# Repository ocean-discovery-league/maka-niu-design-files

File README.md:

# maka-niu-design-files
All files needed to build a Maka Niu

Instructions for fabrication and software installation here.

Link to install image here.
 
Please direct all questions concerning fabrication plans or direct purchase of the Delrin housing to Dr. Allan Adams of Oceanic Labs (allan@oceanic-labs.org)

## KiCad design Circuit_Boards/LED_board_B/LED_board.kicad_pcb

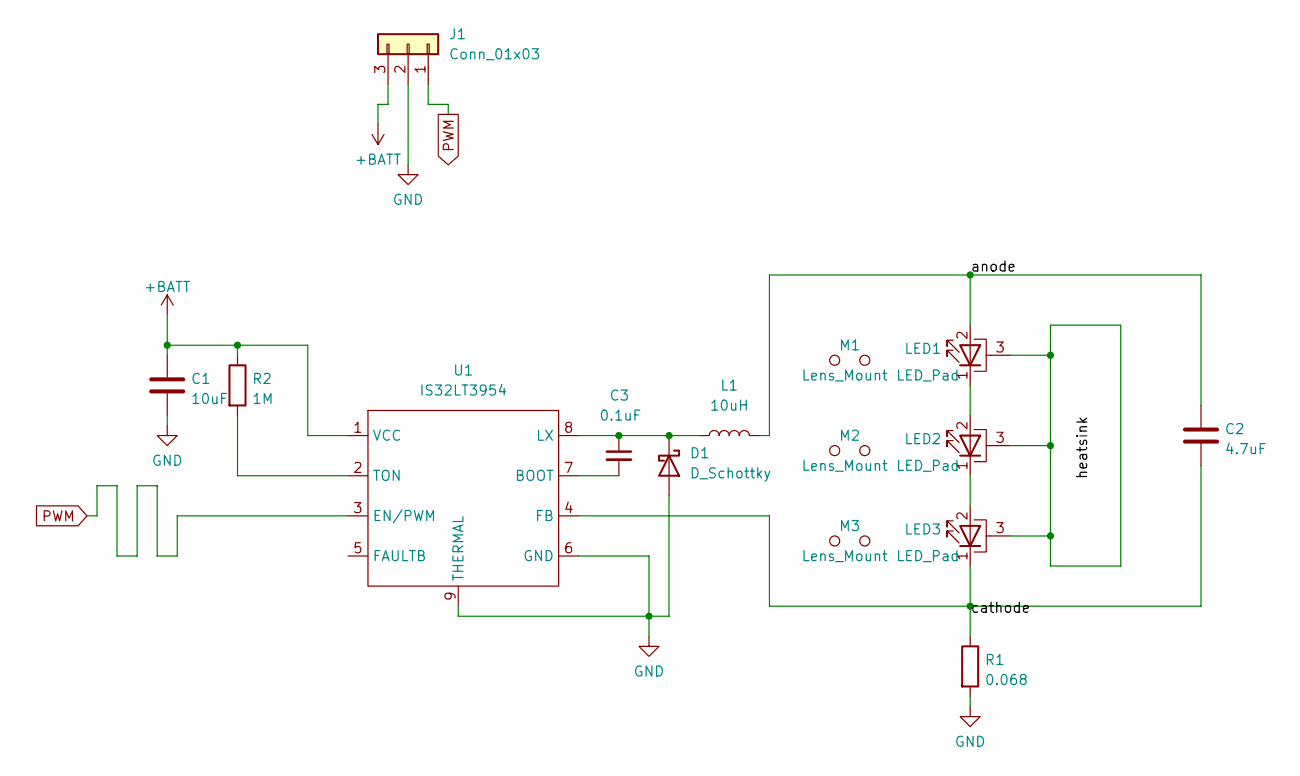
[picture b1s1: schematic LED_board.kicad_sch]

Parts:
C1: 10uF; C_1210_3225Metric; Digikey 13-CC1210KFX7R8BB106CT-ND
C2: 4.7uF; C_1210_3225Metric; Digikey 1276-1292-1-ND
C3: 0.1uF; C_0603_1608Metric; Digikey 1276-1935-1-ND
D1: D_Schottky; D_SMA; Digikey SK54A-LTPMSCT-ND
J1: Conn_01x03; Molex_Micro-Fit_3.0_43650-0324_1x03-1MP_P3.00mm_Vertical; Digikey WM3887CT-ND
L1: 10uH; PA5175_Inductor; Digikey 553-PA5175.103NLTCT-ND
LED1, LED2, LED3: LED_Pad; LED_Cree-XHP50_3V_hand_solder; Digikey XMLBWT-00-0000-0000U2050CT-ND
M1, M2, M3: Lens_Mount; LEDiL_Clip; Digikey 711-FP18200_LISA3-M-CLIP16-ND
R1: 0.068; R_2512_6332Metric; Digikey 311-0.068TCT-ND
R2: 1M; R_0603_1608Metric; Digikey RMCF0603FG1M00CT-ND
U1: IS32LT3954; SOP-8-1EP_4.57x4.57mm_P1.27mm_EP4.57x4.45mm_ThermalVias; Digikey 2521-IS32LT3954-GRLA3-TRCT-ND

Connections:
+BATT: C1.1, J1.3, R2.1, U1.1 (VCC)
/anode: C2.1, L1.2, LED1.2 (A)
/cathode: C2.2, LED3.1 (K), R1.1, U1.4 (FB)
/heatsink: LED1.3 (PAD), LED2.3 (PAD), LED3.3 (PAD)
GND: C1.2, D1.2 (A), J1.2, R1.2, U1.6 (GND), U1.9 (THERMAL)
unnamed: C3.1, D1.1 (K), L1.1, U1.8 (LX)
unnamed: C3.2, U1.7 (BOOT)
unnamed: LED1.1 (K), LED2.2 (A)
unnamed: LED2.1 (K), LED3.2 (A)
unnamed: R2.2, U1.2 (TON)
PWM: J1.1, U1.3 (EN/PWM)

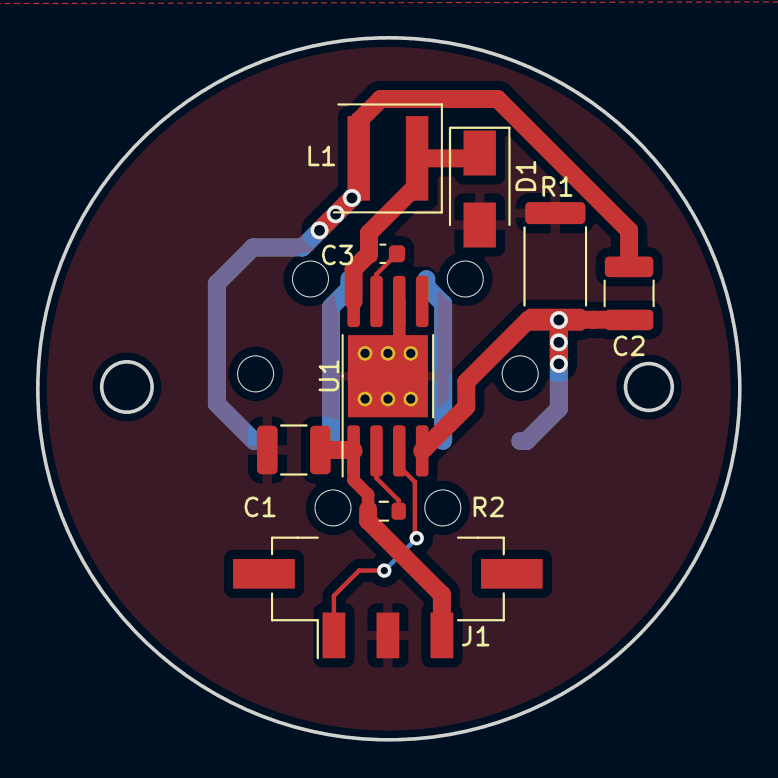
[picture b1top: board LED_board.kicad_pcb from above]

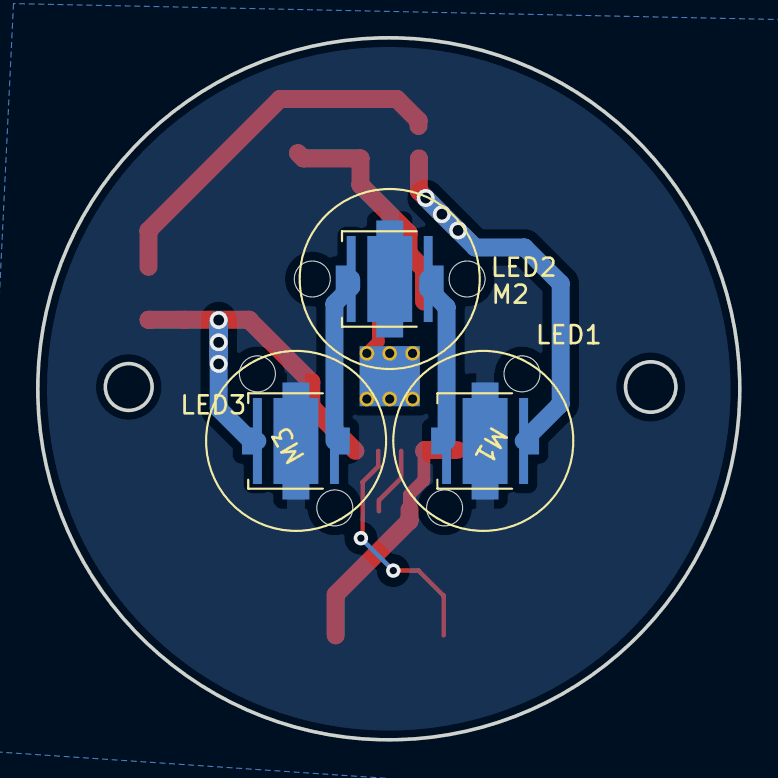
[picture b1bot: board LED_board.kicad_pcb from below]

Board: 2 copper layers, 39.0 x 39.0 mm, 15 parts (6 on the bottom side), 11 nets.

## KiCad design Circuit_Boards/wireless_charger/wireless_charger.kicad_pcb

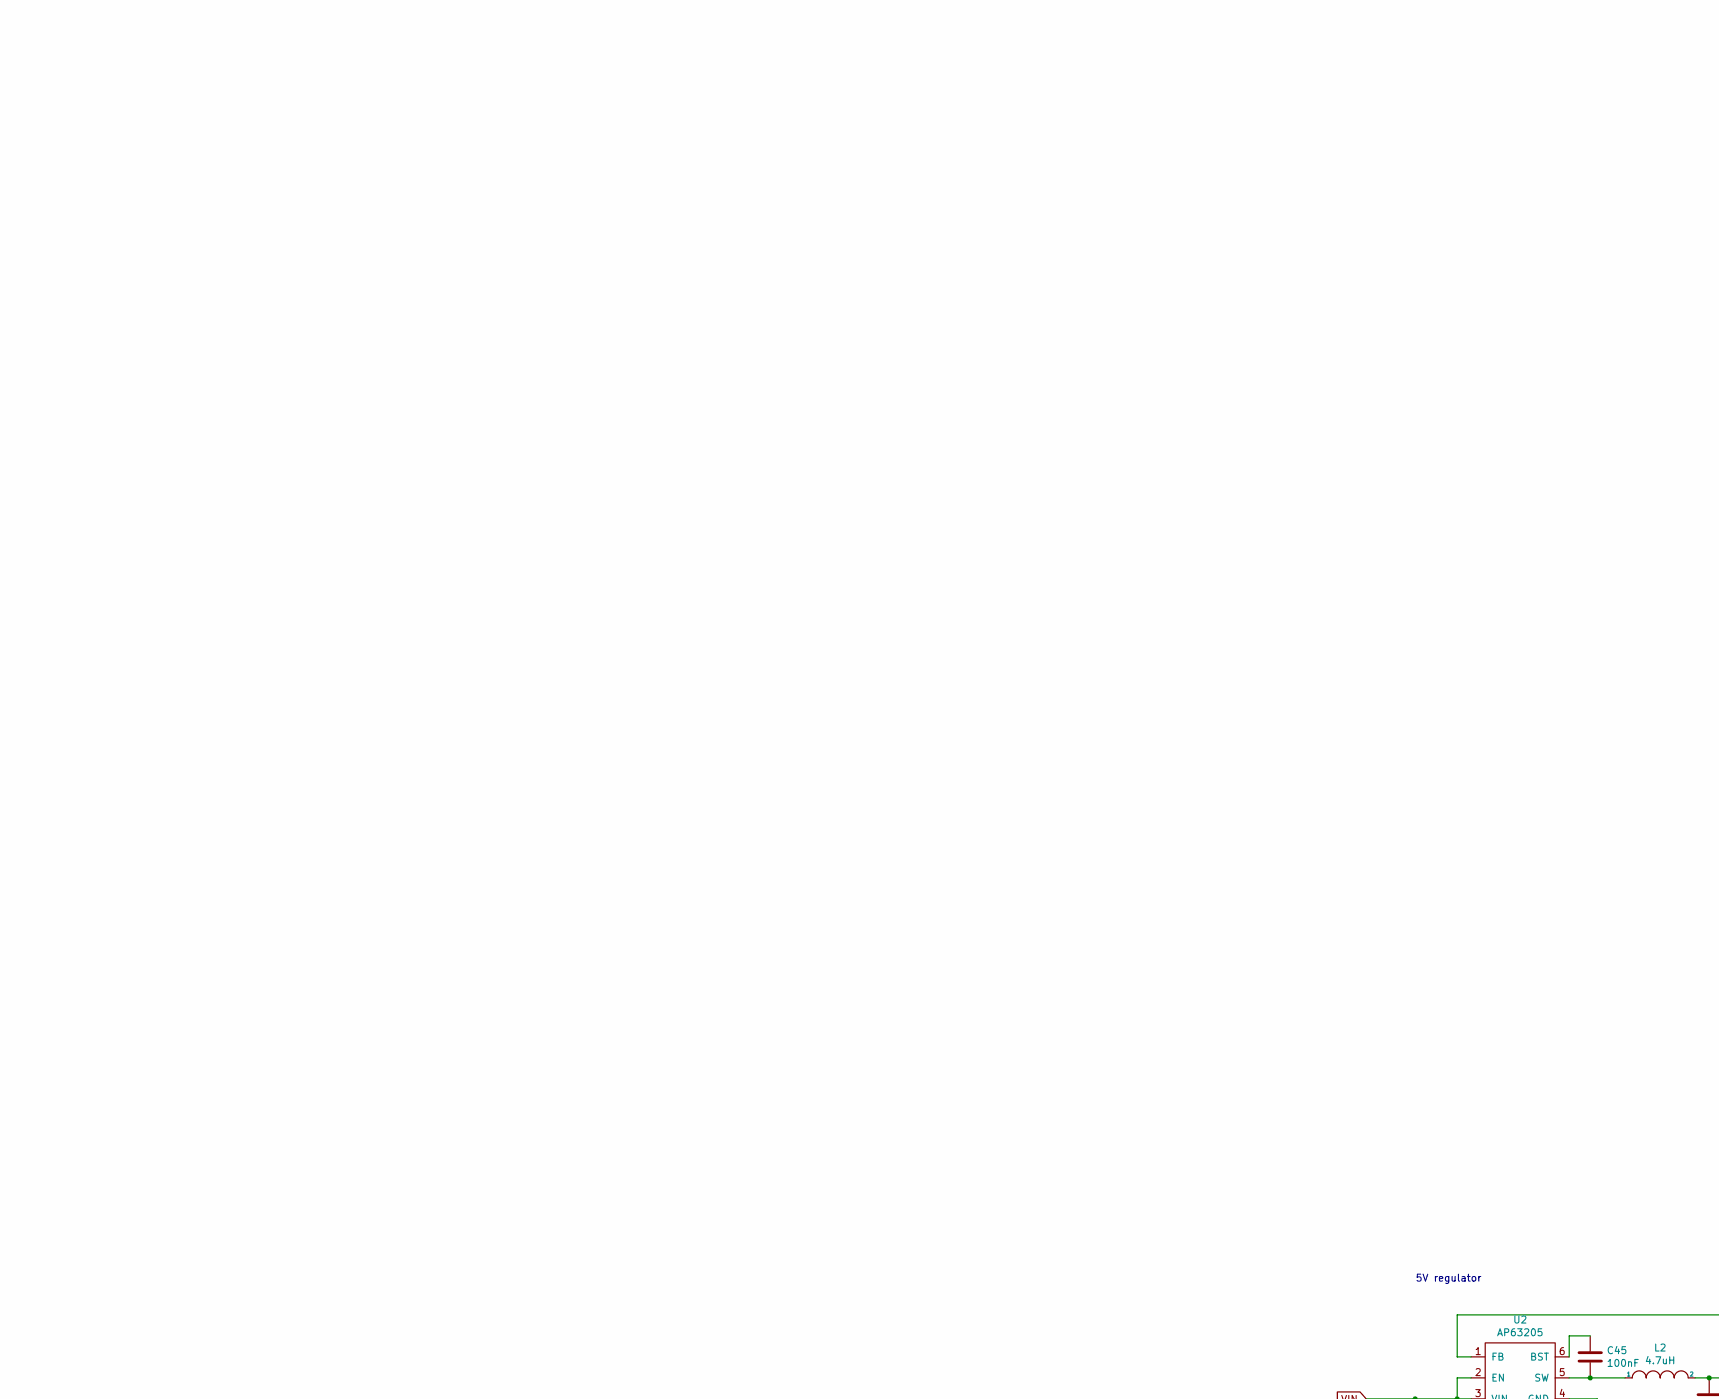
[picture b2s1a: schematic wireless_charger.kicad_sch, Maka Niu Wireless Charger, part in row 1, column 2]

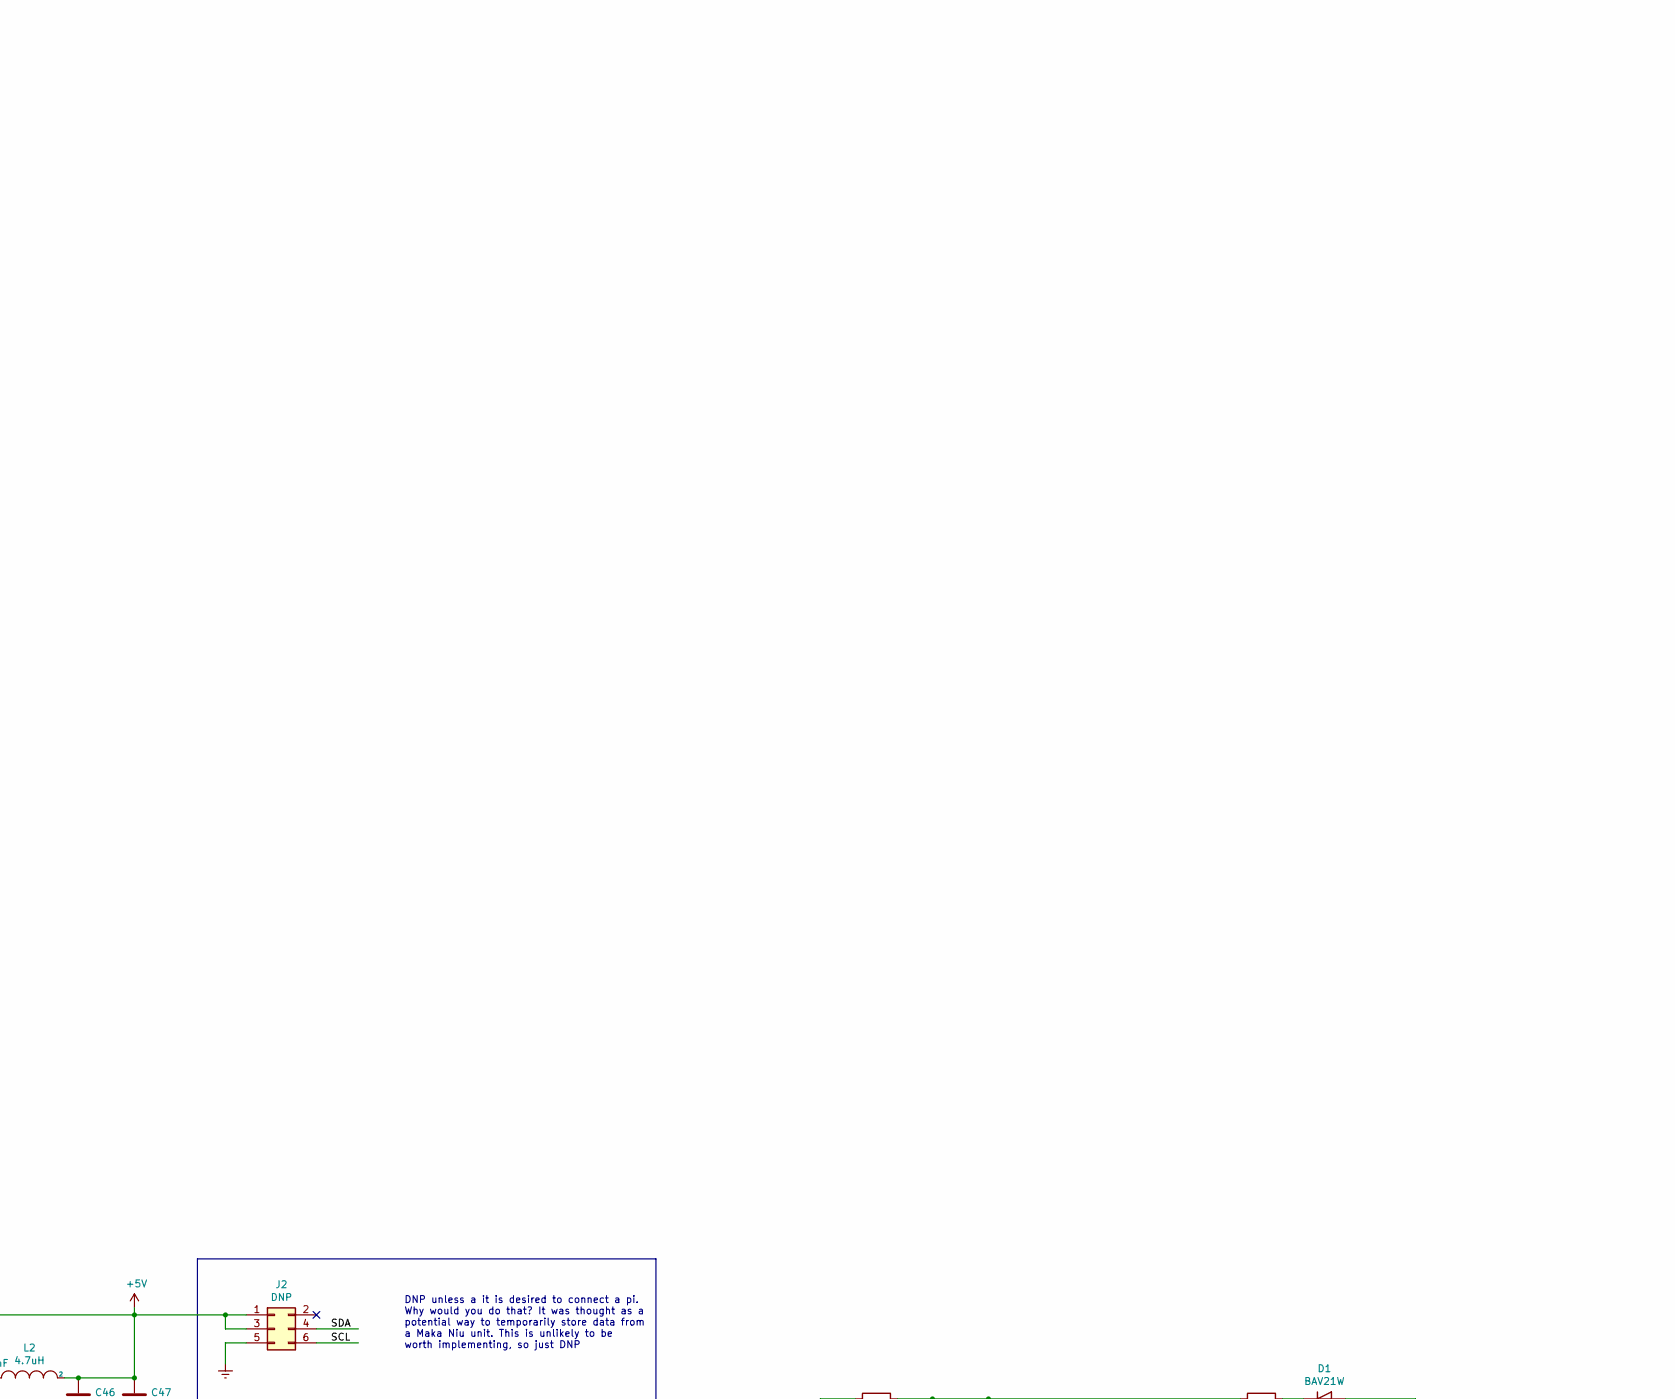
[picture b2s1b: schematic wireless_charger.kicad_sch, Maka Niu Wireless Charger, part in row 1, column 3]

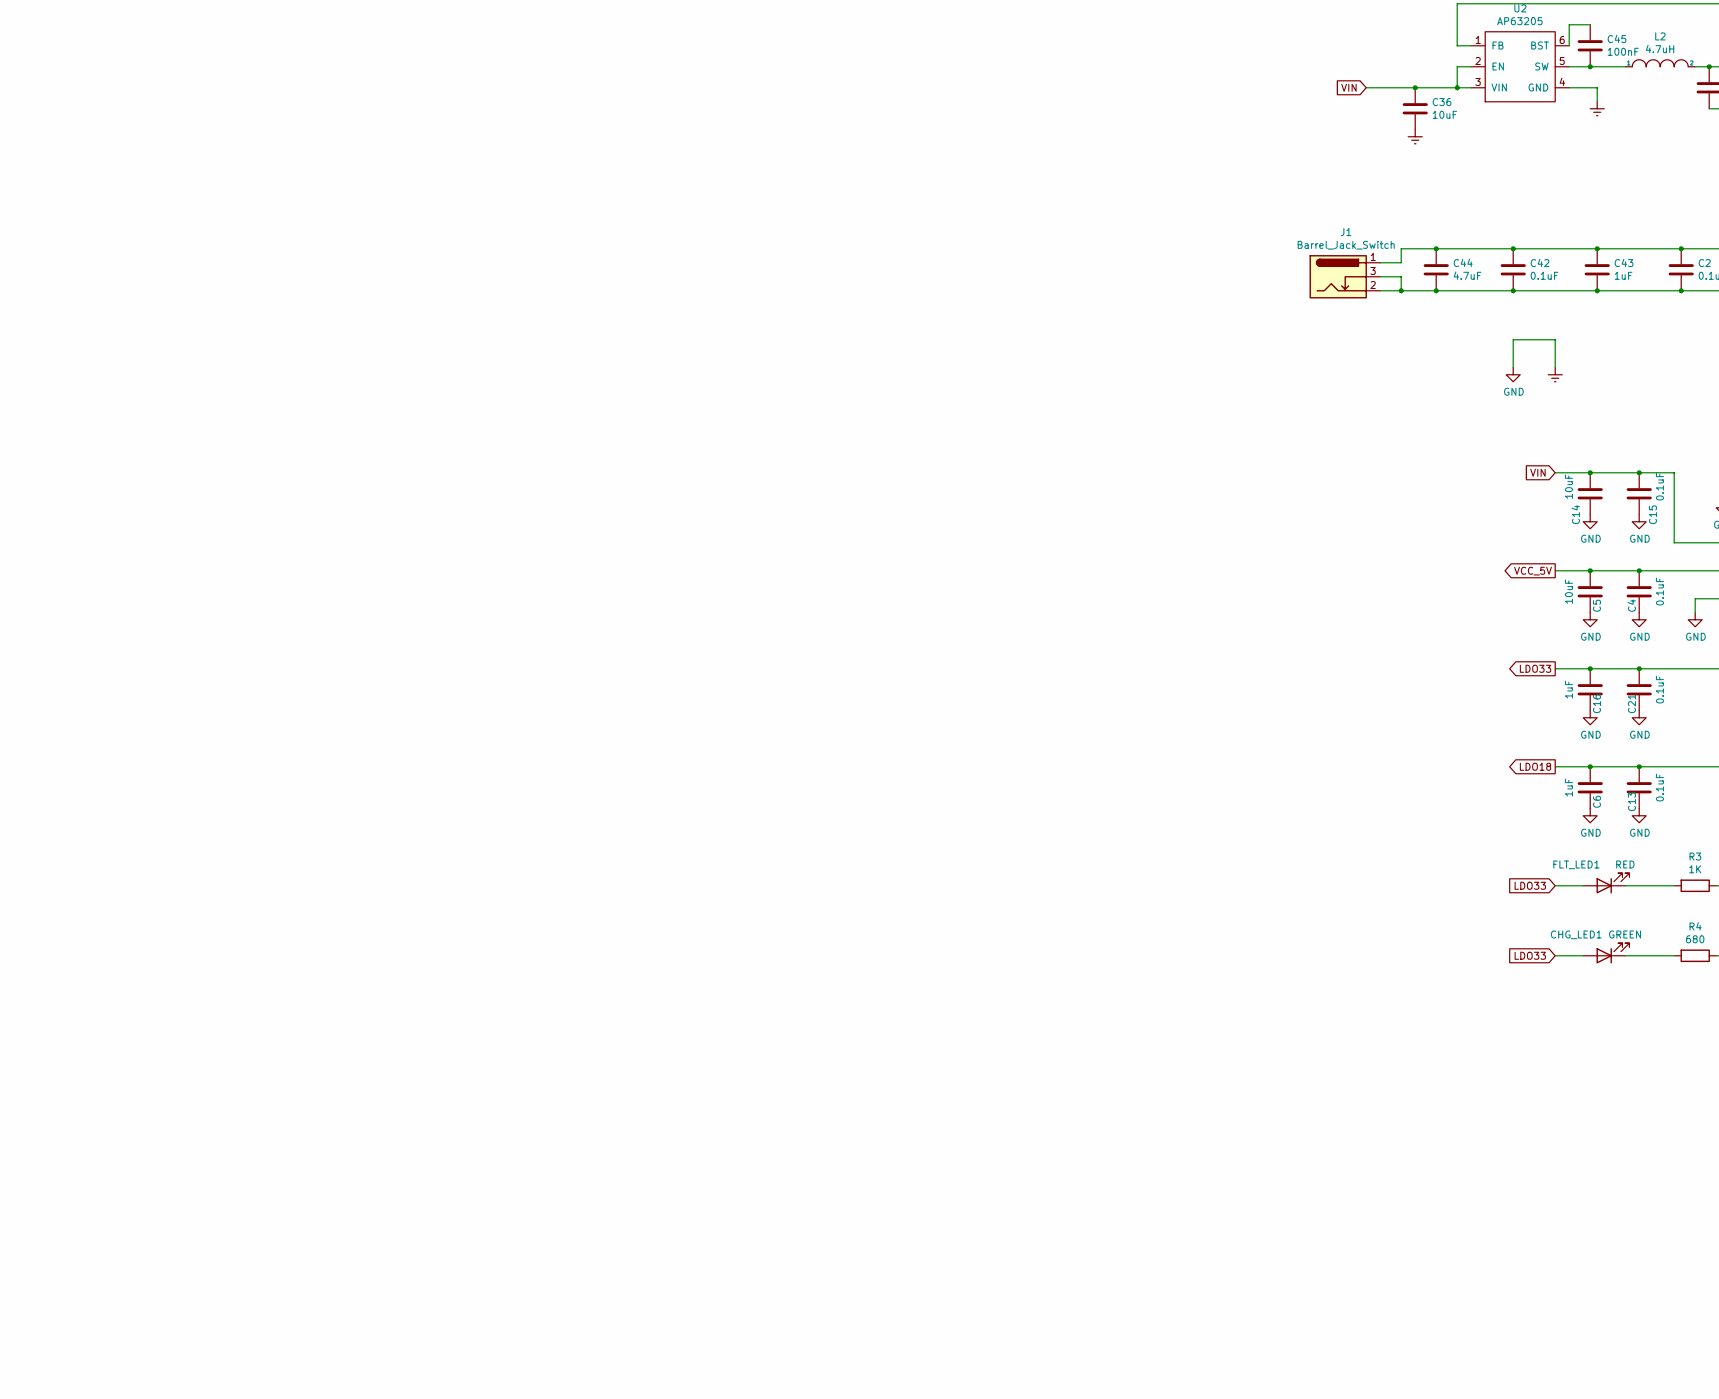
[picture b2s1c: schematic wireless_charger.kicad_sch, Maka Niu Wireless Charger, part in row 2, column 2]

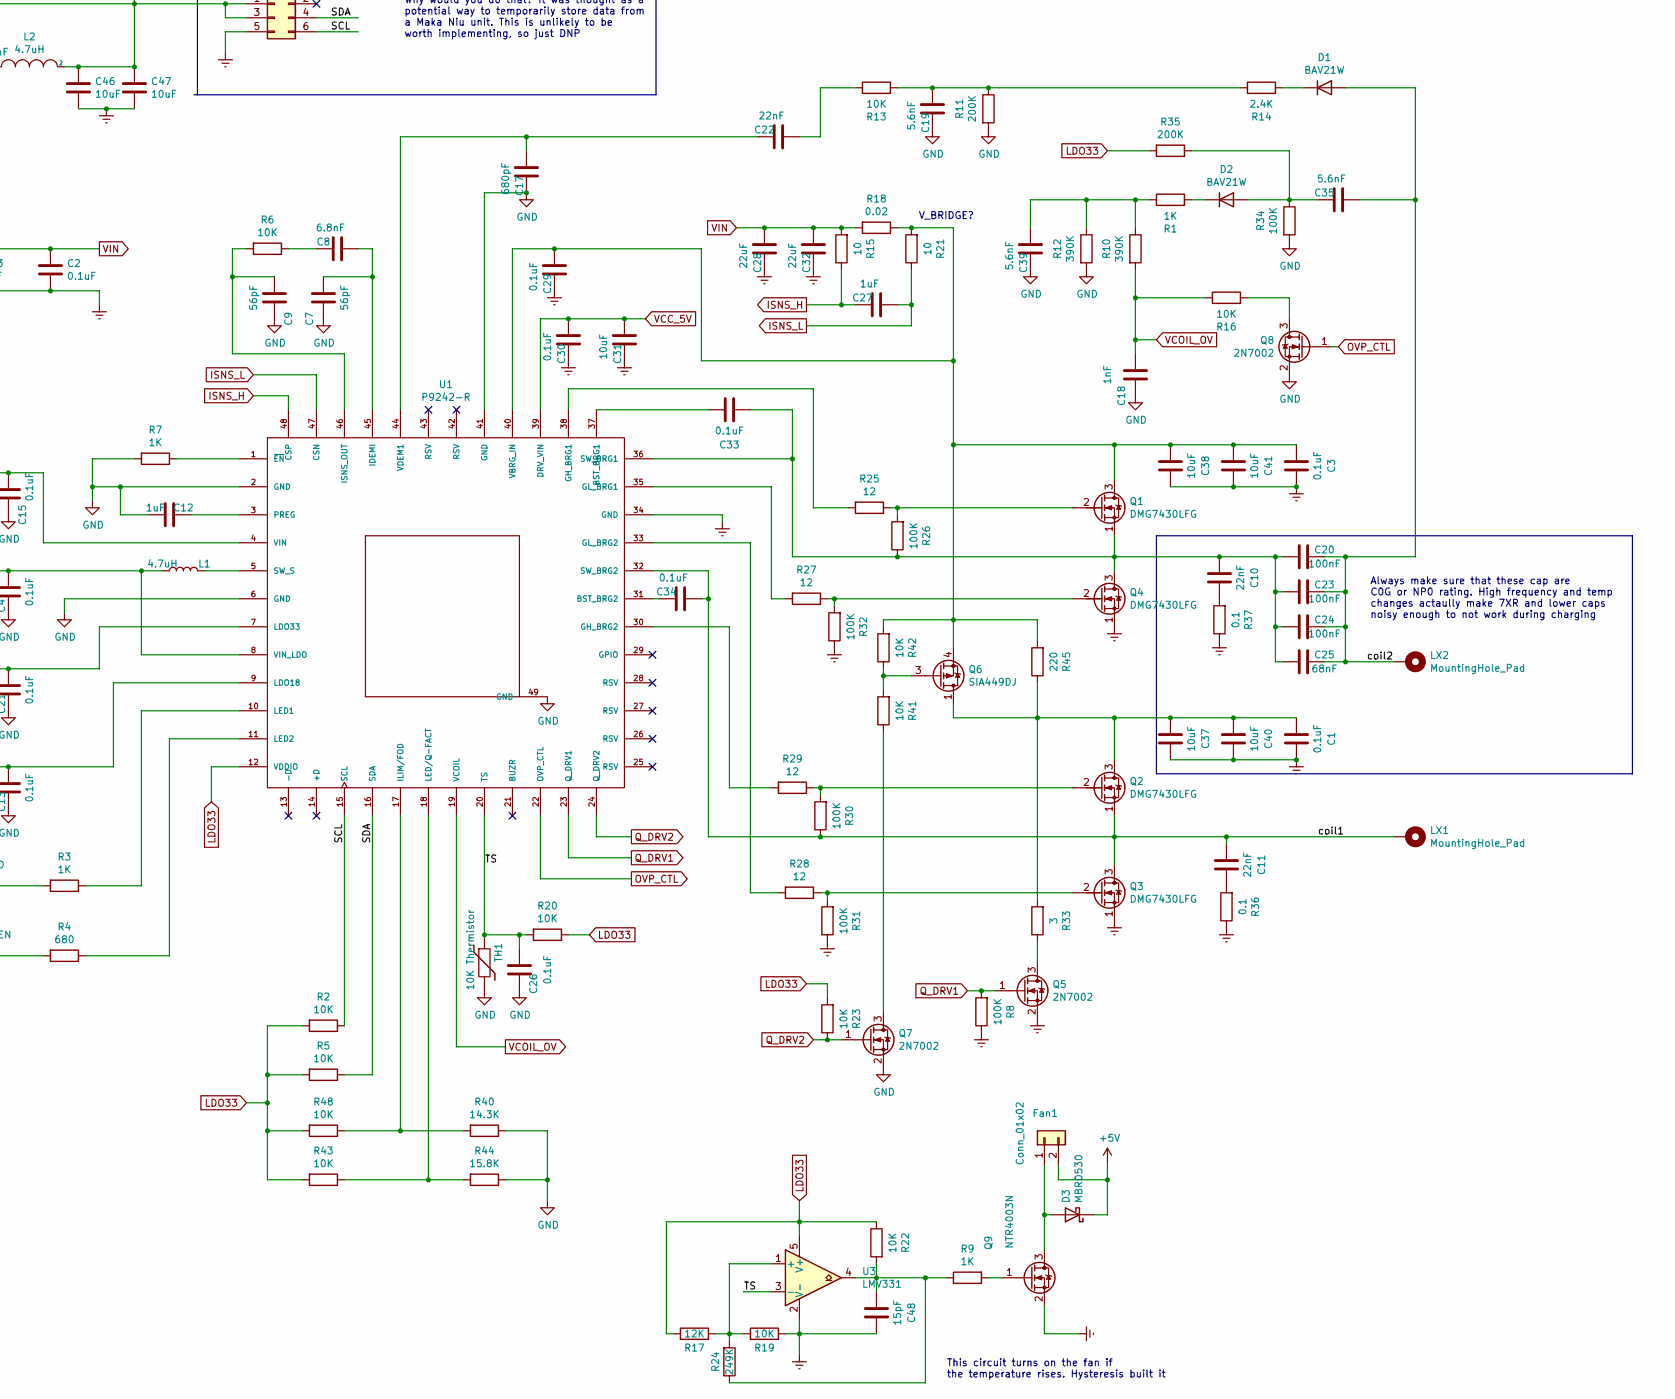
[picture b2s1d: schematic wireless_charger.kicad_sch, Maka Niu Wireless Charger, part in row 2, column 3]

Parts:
C1, C2, C3, C4, C13, C15, C21, C26, C29, C30, C33, C34: 0.1uF; C_0402_1005Metric; Part Number ‎GRM155R71E104KE14D‎; Digikey 490-10698-1-ND
C5, C14, C31, C36, C37, C38, C40, C41, C46, C47: 10uF; C_0603_1608Metric; Part Number ‎GRM188R61E106KA73D; Digikey 490-18214-1-ND
C6, C12, C16, C27: 1uF; C_0402_1005Metric; Part Number ‎CC0402KRX5R8BB104; Digikey 311-1697-1-ND
C7, C9: 56pF; C_0402_1005Metric; Part Number ‎CC0402FRNPO9BN560; Digikey 311-3734-1-ND
C8: 6.8nF; C_0402_1005Metric; Part Number ‎GCM155R71E682KA37D‎; Digikey 490-17758-1-ND
C10, C11: 22nF; C_0603_1608Metric; Part Number CC0603KRX7R9BB223; Digikey 311-1370-1-ND
C17: 680pF; C_0402_1005Metric; Part Number ‎CC0402KRX7R9BB681; Digikey 311-1030-1-ND
C18: 1nF; C_0603_1608Metric; Part Number CL10B102KB8WPJC; Digikey 1276-CL10B102KB8WPJCTR
C19, C35, C39: 5.6nF; C_0603_1608Metric; Part Number ‎C1608C0G2A562J080AE‎; Digikey 445-180278-1-ND
C20, C23, C24: 100nF; C_1206_3216Metric; Part Number ‎GRM31C5C2A104JA01L‎; Digikey 490-16315-1-ND
C22: 22nF; C_0402_1005Metric; Part Number ‎GRM155R71H223KA12J‎; Digikey 490-6360-1-ND
C25: 68nF; C_1206_3216Metric; Part Number ‎C3216C0G2A683J160AC; Digikey 445-172675-1-ND
C28, C32: 22uF; C_1206_3216Metric; Part Number ‎CL31A226KAHNNNE; Digikey 1276-3047-1-ND
C42: 0.1uF; C_0603_1608Metric; Part Number ‎CC0603KPX7R9BB104‎; Digikey 311-3567-1-ND
C43: 1uF; C_0603_1608Metric; Part Number ‎CL10A105KA8NNNC; Digikey 1276-1102-1-ND
C44: 4.7uF; C_0603_1608Metric; Part Number CAP CER 4.7UF 25V X5R 0603; Digikey 490-7203-1-ND
C45: 100nF; C_0603_1608Metric; Part Number CL10B104KB8NNNL; Digikey 1276-CL10B104KB8NNNLTR
C48: 15pF; C_0402_1005Metric; Part Number ‎CC0402GRNPO9BN150‎; Digikey 311-1649-1-ND
CHG_LED1: GREEN; LED_0603_1608Metric; Part Number LTST-S270KGKT; Digikey 160-1478-1-ND
D1, D2: BAV21W; D_SOD-123; Part Number ‎BAV21W-7-F‎; Digikey BAV21W-7-F‎
D3: MBR0530; D_SOD-123; Part Number ‎MBR0530T1G; Digikey MBR0530T1GOSCT-ND
FLT_LED1: RED; LED_0603_1608Metric; Part Number LTST-S270EKT; Digikey 160-1474-1-N
Fan1: Conn_01x02; PinHeader_1x02_P2.54mm_Vertical; Digikey DNP
J1: Barrel_Jack_Switch; CUI_PJ-002AH; Part Number ‎PJ-002AH; Digikey CP-002AH-ND
J2: DNP; PinHeader_2x03_P2.54mm_Vertical; Part Number ‎PPTC032LFBN-RC‎; Digikey S7071-ND
L1: 4.7uH; L_0603_1608Metric; Part Number ‎LQM18PN4R7MFR; Digikey 490-12065-1-ND
L2: 4.7uH; L_1008_2520Metric; Part Number ‎DFE252012P-4R7M=P2‎; Digikey 490-10651-1-ND
LX1, LX2: MountingHole_Pad; TestPoint_THTPad_D2.0mm_Drill1.0mm; Digikey DNP
Q1, Q2, Q3, Q4: DMG7430LFG; TRANS_DMP3017SFGQ-7_b; Part Number ‎DMG7430LFG-7; Digikey DMG7430LFG-7‎
Q5, Q7, Q8: 2N7002; SOT-23; Part Number ‎2N7002KT1G; Digikey 2N7002KT1GOSCT-ND
Q6: SIA449DJ; Vishay_PowerPAK_SC70-6L_Single; Part Number ‎SIA449DJ-T1-GE3‎; Digikey SIA449DJ-T1-GE3CT-ND
Q9: NTR4003N; SOT-23; Part Number ‎NTR4003NT1G; Digikey NTR4003NT1GOSCT-ND
R1, R3, R7, R9: 1K; R_0402_1005Metric; Part Number ‎RC0402JR-071KL; Digikey 311-1.0KJRCT-ND
R2, R5, R6, R13, R16, R19, R20, R22, R23, R41, R42, R43, R48: 10K; R_0402_1005Metric; Part Number ‎RC0402FR-0710KL; Digikey 311-10.0KLRCT-ND
R4: 680; R_0402_1005Metric; Part Number ‎RC0402JR-07680RL; Digikey 311-680JRCT-ND
R8, R26, R30, R31, R32: 100K; R_0402_1005Metric; Part Number ‎ERJ-2GEJ104X; Digikey P100KJCT-ND
R10, R12: 390K; R_0603_1608Metric; Part Number ‎ERJ-3GEYJ394V‎; Digikey P390KGCT-ND
R11, R35: 200K; R_0603_1608Metric; Part Number ‎RC0603FR-07200KL; Digikey 311-200KHRCT-ND
R14: 2.4K; R_0402_1005Metric; Part Number ‎ERJ-2GEJ242X; Digikey P2.4KJCT-ND
R15, R21: 10; R_0402_1005Metric; Part Number ‎ERJ-2RKF10R0X; Digikey P10.0LCT-ND
R17: 12K; R_0402_1005Metric; Part Number RC0402FR-0712KL; Digikey 311-12.0KLRCT-ND
R18: 0.02; R_0805_2012Metric; Part Number ‎WSL0805R0200FEA‎; Digikey WSLA-.02CT-ND
R24: 249K; R_0402_1005Metric; Digikey CR0402-FX-2493GLFCT-ND
R25, R27, R28, R29: 12; R_0402_1005Metric; Part Number ‎ERJ-2GEJ120X; Digikey P12JCT-ND
R33: 3; R_0805_2012Metric; Part Number ‎RC0805FR-073RL; Digikey 311-3.00CRCT-ND
R34: 100K; R_0603_1608Metric; Part Number ‎ERJ-3EKF1003V; Digikey P100KHCT-ND
R36, R37: 0.1; R_0402_1005Metric; Part Number ‎ERJ-2BSJR10X‎; Digikey P17359CT-ND
R40: 14.3K; R_0402_1005Metric; Part Number CRCW040214K3FKED; Digikey 541-14.3KLTR-ND
R44: 15.8K; R_0402_1005Metric; Part Number RC0402FR-0715K8L; Digikey YAG2993TR-ND
R45: 220; R_0805_2012Metric; Part Number RCS0805220RFKEA; Digikey 541-10516-2-ND
TH1: 10K Thermistor; R_0805_2012Metric; Part Number ‎NB12K00103KBB; Digikey 478-NB12K00103KBBCT-ND
U1: P9242-R; QFN40P600X600X100-49N; Part Number P9242-R
U2: AP63205; TSOT-23-6; Part Number ‎AP63205WU-7; Digikey AP63205WU-7DICT-ND
U3: LMV331; SOT-23-5; Part Number ‎LMV331IDBVR‎; Digikey 296-6633-1-ND

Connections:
+5V: C46.2, C47.2, D3.1 (K), Fan1.2, J2.1, J2.3, L2.2, U2.1 (FB)
/SCL: J2.6, R2.1, U1.15 (SCL)
/SDA: J2.4, R5.1, U1.16 (SDA)
/TS: C26.2, R20.2, TH1.1, U1.20 (TS), U3.3 (-)
/coil1: C11.2, C34.2, LX1.1, Q2.1 (S), Q3.3 (D), R30.1, U1.32 (SW_BRG2)
/coil2: C20.2, C23.2, C24.2, C25.2, C35.2, D1.2 (A), LX2.1
Earth: C1.1, C2.2, C3.1, C4.1, C5.1, C6.1, C7.1, C9.1, C12.2, C13.1, C14.1, C15.1, C16.1, C17.1, C18.1, C19.1, C21.1, C26.1, C28.1, C29.1, C30.1, C31.1, C32.1, C36.1, C37.1, C38.1, C39.1, C40.1, C41.1, C42.2, C43.2, C44.2, C46.1, C47.1, C48.1, J1.2, J1.3, J2.5, Q3.1 (S), Q4.1 (S), Q5.2 (S), Q7.2 (S), Q8.2 (S), Q9.2 (S), R7.2, R8.1, R11.2, R12.2, R19.1, R31.1, R32.1, R34.2, R36.1, R37.1, R40.1, R44.1, TH1.2, U1.2 (GND), U1.6 (GND), U1.34 (GND), U1.41 (GND), U1.49 (GND), U2.4 (GND), U3.2 (V-)
ISNS_H: C27.1, R15.1, U1.48 (CSP)
ISNS_L: C27.2, R21.1, U1.47 (CSN)
LDO18: C6.2, C13.2, U1.9 (LDO18)
LDO33: C16.2, C21.2, CHG_LED1.2 (A), FLT_LED1.2 (A), R2.2, R5.2, R17.2, R20.1, R22.1, R23.2, R35.2, R43.2, R48.2, U1.7 (LDO33), U1.12 (VDDIO), U3.5 (V+)
unnamed: C1.2, C37.2, C40.2, Q2.3 (D), Q6.1 (D), R33.2, R45.1
unnamed: C7.2, C8.2, U1.45 (IDEMI)
unnamed: C8.1, R6.1
unnamed: C9.2, R6.2, U1.46 (ISNS_OUT)
unnamed: C10.1, R37.2
unnamed: C10.2, C20.1, C23.1, C24.1, C25.1, C33.2, Q1.1 (S), Q4.3 (D), R26.1, U1.36 (SW_BRG1)
unnamed: C11.1, R36.2
unnamed: C12.1, U1.3 (PREG)
unnamed: C17.2, C22.1, U1.44 (VDEM1)
unnamed: C19.2, R11.1, R13.2, R14.1
unnamed: C22.2, R13.1
unnamed: C3.2, C29.2, C38.2, C41.2, Q1.3 (D), Q6.4 (S), R18.1, R21.2, R42.2, R45.2, U1.40 (VBRG_IN)
unnamed: C33.1, U1.37 (BST_BRG1)
unnamed: C34.1, U1.31 (BST_BRG2)
unnamed: C35.1, D2.2 (A), R34.1, R35.1
unnamed: C39.2, R1.1, R10.1, R12.1
unnamed: C45.1, L2.1, U2.5 (SW)
unnamed: C45.2, U2.6 (BST)
unnamed: C48.2, R9.1, R22.2, R24.1, U3.4
unnamed: CHG_LED1.1 (K), R4.2
unnamed: D1.1 (K), R14.2
unnamed: D2.1 (K), R1.2
unnamed: D3.2 (A), Fan1.1, Q9.3 (D)
unnamed: FLT_LED1.1 (K), R3.2
unnamed: L1.2, U1.5 (SW_S)
unnamed: Q1.2 (G), R25.1, R26.2
unnamed: Q2.2 (G), R29.1, R30.2
unnamed: Q3.2 (G), R28.1, R31.2
unnamed: Q4.2 (G), R27.1, R32.2
unnamed: Q5.3 (D), R33.1
unnamed: Q6.3 (G), R41.2, R42.1
unnamed: Q7.3 (D), R41.1
unnamed: Q8.3 (D), R16.2
unnamed: Q9.1 (G), R9.2
unnamed: R3.1, U1.10 (LED1)
unnamed: R4.1, U1.11 (LED2)
unnamed: R7.1, U1.1 (~EN)
unnamed: R17.1, R19.2, R24.2, U3.1 (+)
unnamed: R25.2, U1.38 (GH_BRG1)
unnamed: R27.2, U1.35 (GL_BRG1)
unnamed: R28.2, U1.33 (GL_BRG2)
unnamed: R29.2, U1.30 (GH_BRG2)
unnamed: R40.2, R48.1, U1.17 (ILIM/FOD)
unnamed: R43.1, R44.2, U1.18 (LED/Q-FACT)
OVP_CTL: Q8.1 (G), U1.22 (OVP_CTL)
Q_DRV1: Q5.1 (G), R8.2, U1.23 (Q_DRV1)
Q_DRV2: Q7.1 (G), R23.1, U1.24 (Q_DRV2)
VCC_5V: C4.2, C5.2, C30.2, C31.2, L1.1, U1.8 (VIN_LDO), U1.39 (DRV_VIN)
VCOIL_OV: C18.2, R10.2, R16.1, U1.19 (VCOIL)
VIN: C2.1, C14.2, C15.2, C28.2, C32.2, C36.2, C42.1, C43.1, C44.1, J1.1, R15.2, R18.2, U1.4 (VIN), U2.2 (EN), U2.3 (VIN)

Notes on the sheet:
DNP unless a it is desired to connect a pi. Why would you do that? It was thought as a potential way to temporarily store data from a Maka Niu unit. This is unlikely to be worth implementing, so just DNP
V_BRIDGE?
5V regulator
This circuit turns on the fan if the temperature rises. Hysteresis built it
Always make sure that these cap are C0G or NP0 rating. High frequency and temp changes actaully make 7XR and lower caps noisy enough to not work during charging

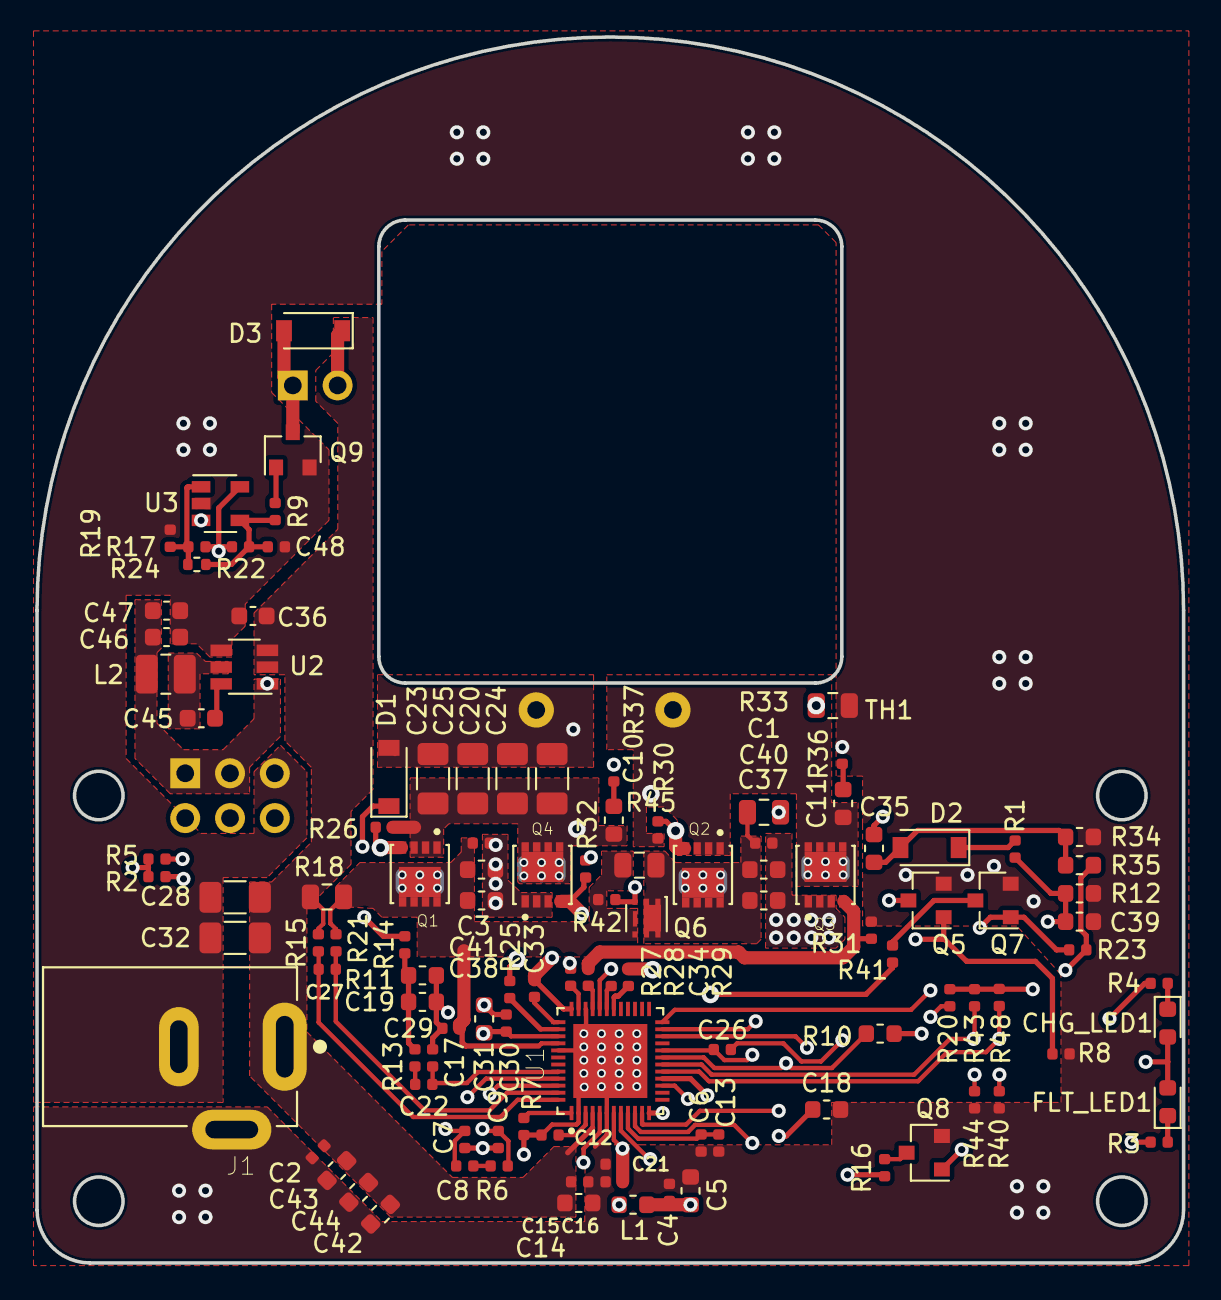
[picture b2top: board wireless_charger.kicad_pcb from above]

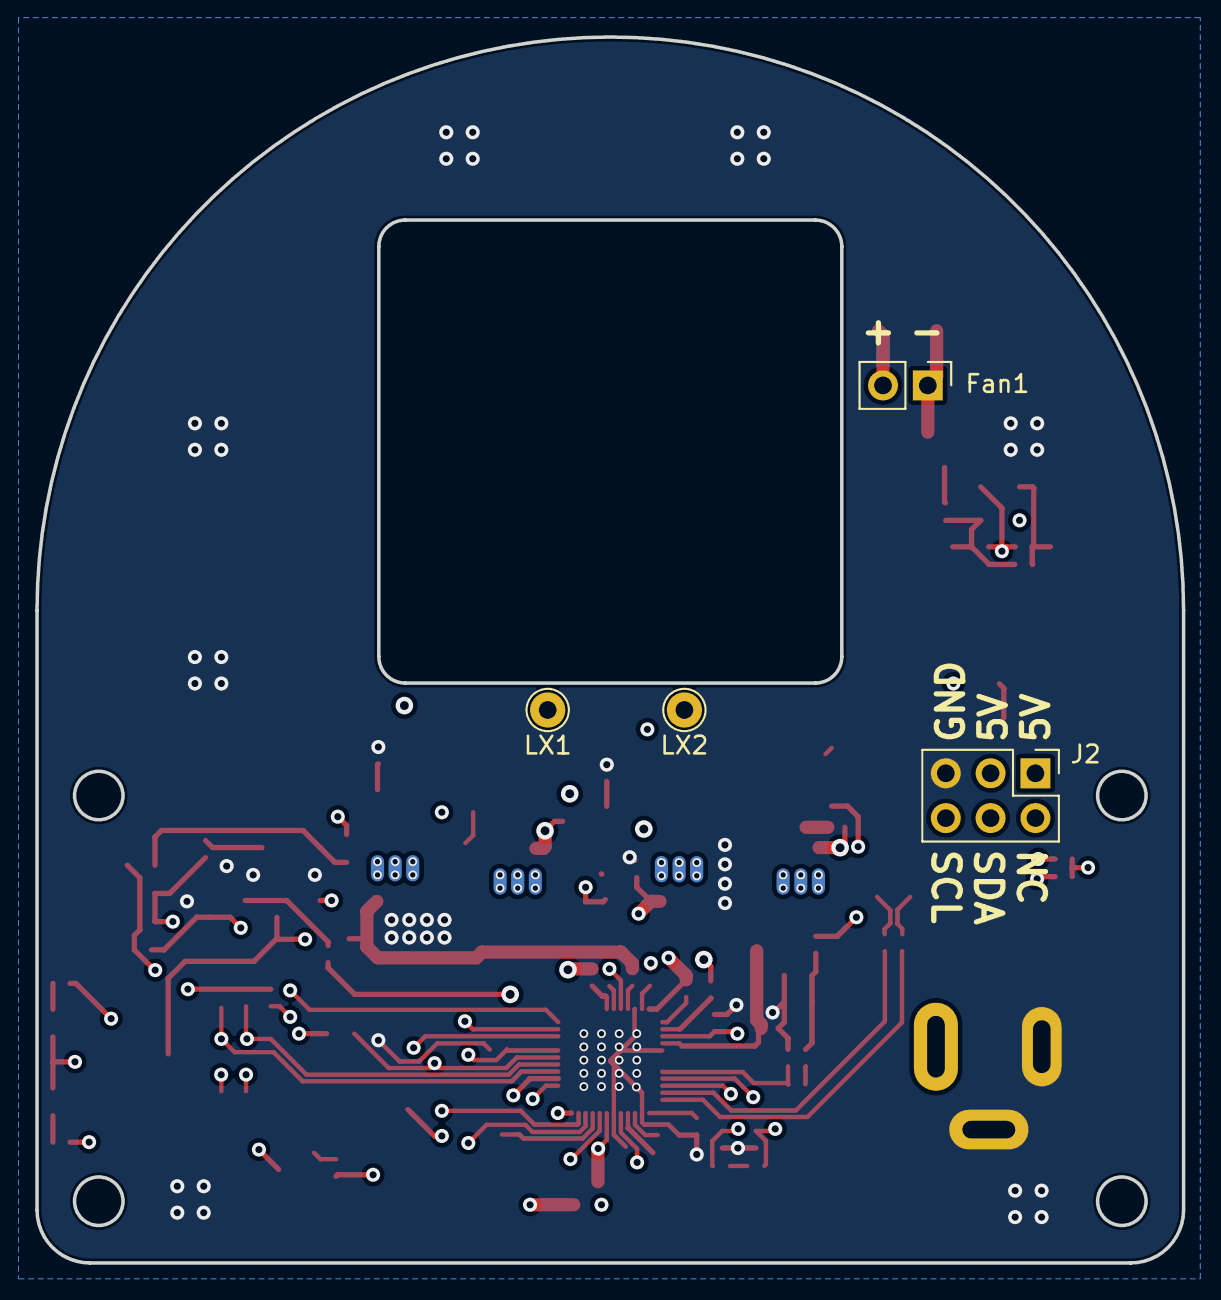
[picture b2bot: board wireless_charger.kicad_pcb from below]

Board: 4 copper layers, 65.0 x 69.5 mm, 117 parts (4 on the bottom side), 61 nets.
